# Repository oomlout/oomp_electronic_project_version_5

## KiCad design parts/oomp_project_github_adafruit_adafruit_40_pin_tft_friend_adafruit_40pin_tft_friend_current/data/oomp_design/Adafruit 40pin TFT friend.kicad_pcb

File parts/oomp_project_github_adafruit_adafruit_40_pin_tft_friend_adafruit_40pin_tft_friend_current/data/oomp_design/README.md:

# OOMP KiCad design copy

Open `Adafruit 40pin TFT friend.kicad_pro` (or the `.kicad_pcb` / `.kicad_sch`) in KiCad. Local OOMP libraries are under `libraries/`. Original inputs are preserved in [../original/](../original/).

Only verified unchanged installed KiCad defaults were renamed. Modified, custom, unmatched and unavailable items remain unchanged. Soldering variants are never swapped during conversion. Existing pad coordinates, nets and UUIDs are preserved.

See [conversion_report.yaml](conversion_report.yaml) for every conversion and skip. Copy this directory before editing; regeneration refuses to overwrite edited design files.

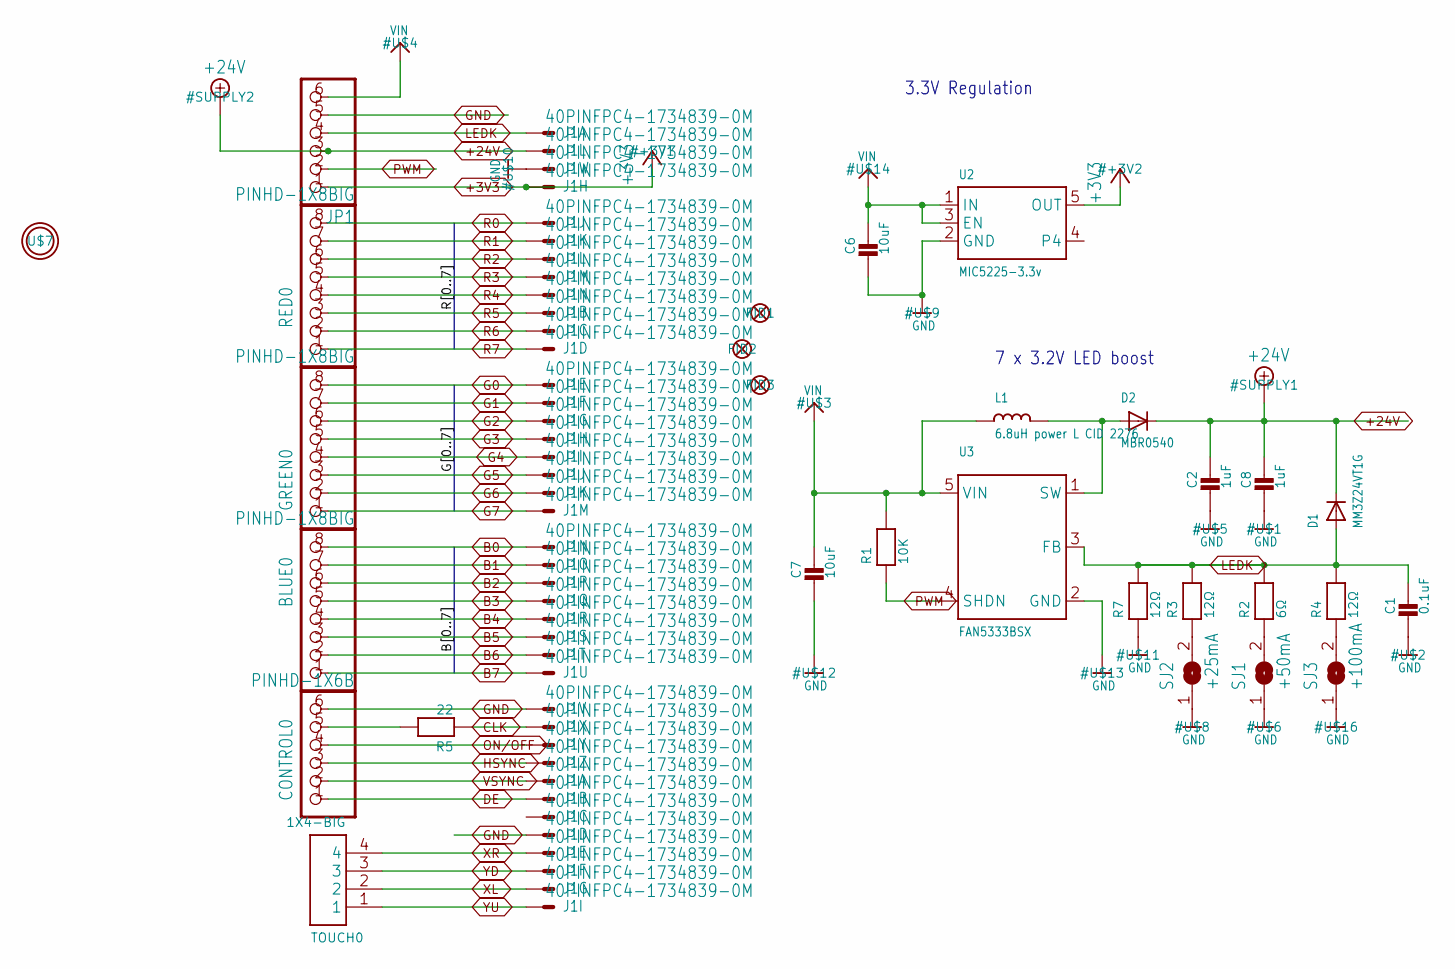
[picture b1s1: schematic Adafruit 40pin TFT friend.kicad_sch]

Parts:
BLUE0: PINHD-1X8BIG; 1X08-BIG
C1: 0.1uF; _0805MP
C2, C8: 1uF; _0805MP
C6, C7: 10uF; _0805MP
CONTROL0: PINHD-1X6B; 1X06-BIG
D1: MM3Z24VT1G; SMADIODE
D2: MBR0540; SOD-123
FID1, FID2, FID3: FIDUCIAL""; FIDUCIAL_1MM
GREEN0: PINHD-1X8BIG; 1X08-BIG
J1: 40PINFPC4-1734839-0M; 4-1734839-0
JP1: PINHD-1X6B; 1X06-BIG
L1: 6.8uH power L CID 2276; INDUCTOR_5X5MM_NR5040_NOTHERMALS
R1: 10K; _0805MP
R2: 6Ω; _0805MP
R3, R4, R7: 12Ω; _0805MP
R5: 22; _0805MP
RED0: PINHD-1X8BIG; 1X08-BIG
SJ1: +50mA; SOLDERJUMPER_ARROW_NOPASTE
SJ2: +25mA; SOLDERJUMPER_ARROW_NOPASTE
SJ3: +100mA; SOLDERJUMPER_ARROW_NOPASTE
TOUCH0: 1X4-BIG; 1X04-BIG
U2: MIC5225-3.3v; SOT23-5
U3: FAN5333BSX; SOT23-5@1
U$7: MOUNTINGHOLE2.5; MOUNTINGHOLE_2.5_PLATED

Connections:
+3V3: J1.4 (MS), JP1.1, U2.5 (OUT)
+24V: C2.1, C8.1, D1.C, D2.C, J1.2 (MS), JP1.3
B0: BLUE0.8, J1.21 (MS)
B1: BLUE0.7, J1.22 (MS)
B2: BLUE0.6, J1.23 (MS)
B3: BLUE0.5, J1.24 (MS)
B4: BLUE0.4, J1.25 (MS)
B5: BLUE0.3, J1.26 (MS)
B6: BLUE0.2, J1.27 (MS)
B7: BLUE0.1, J1.28 (MS)
CLK: J1.30 (MS), R5.1
DE: CONTROL0.1, J1.34 (MS)
G0: GREEN0.8, J1.13 (MS)
G1: GREEN0.7, J1.14 (MS)
G2: GREEN0.6, J1.15 (MS)
G3: GREEN0.5, J1.16 (MS)
G4: GREEN0.4, J1.17 (MS)
G5: GREEN0.3, J1.18 (MS)
G6: GREEN0.2, J1.19 (MS)
G7: GREEN0.1, J1.20 (MS)
GND: C1.2, C2.2, C6.2, C7.2, C8.2, CONTROL0.6, J1.3 (MS), J1.29 (MS), J1.36 (MS), JP1.5, R7.1, SJ1.1, SJ2.1, SJ3.1, U2.2 (GND), U3.2 (GND)
HSYNC: CONTROL0.3, J1.32 (MS)
LEDK: C1.1, D1.A, J1.1 (MSV), JP1.4, R2.2, R3.2, R4.2, R7.2, U3.3 (FB)
unnamed: R2.1, SJ1.2
unnamed: R3.1, SJ2.2
unnamed: R4.1, SJ3.2
unnamed: CONTROL0.5, R5.2
unnamed: D2.A, L1.P$2 (2), U3.1 (SW)
ON/OFF: CONTROL0.4, J1.31 (MS)
PWM: JP1.2, R1.1, U3.4 (SHDN)
R0: J1.5 (MS), RED0.8
R1: J1.6 (MS), RED0.7
R2: J1.7 (MS), RED0.6
R3: J1.8 (MS), RED0.5
R4: J1.9 (MS), RED0.4
R5: J1.10 (MS), RED0.3
R6: J1.11 (MS), RED0.2
R7: J1.12 (MS), RED0.1
VIN: C6.1, C7.1, JP1.6, L1.P$1 (1), R1.2, U2.1 (IN), U2.3 (EN), U3.5 (VIN)
VSYNC: CONTROL0.2, J1.33 (MS)
XL: J1.39 (MS), TOUCH0.2
XR: J1.37 (MS), TOUCH0.4
YD: J1.38 (MS), TOUCH0.3
YU: J1.40 (MS), TOUCH0.1

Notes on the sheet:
3.3V Regulation
7 x 3.2V LED boost

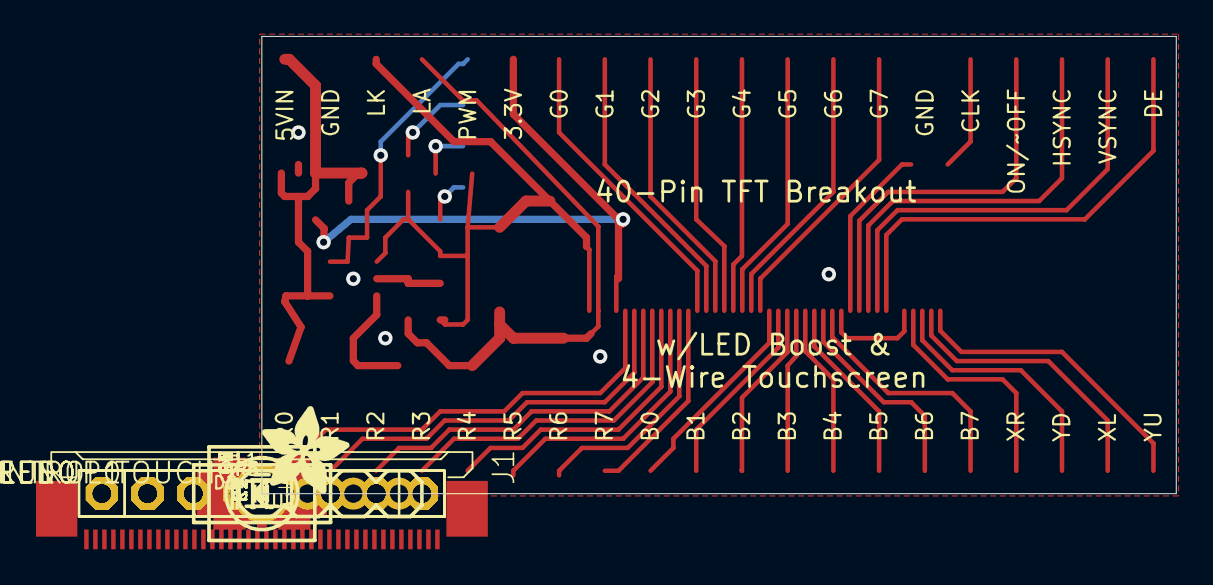
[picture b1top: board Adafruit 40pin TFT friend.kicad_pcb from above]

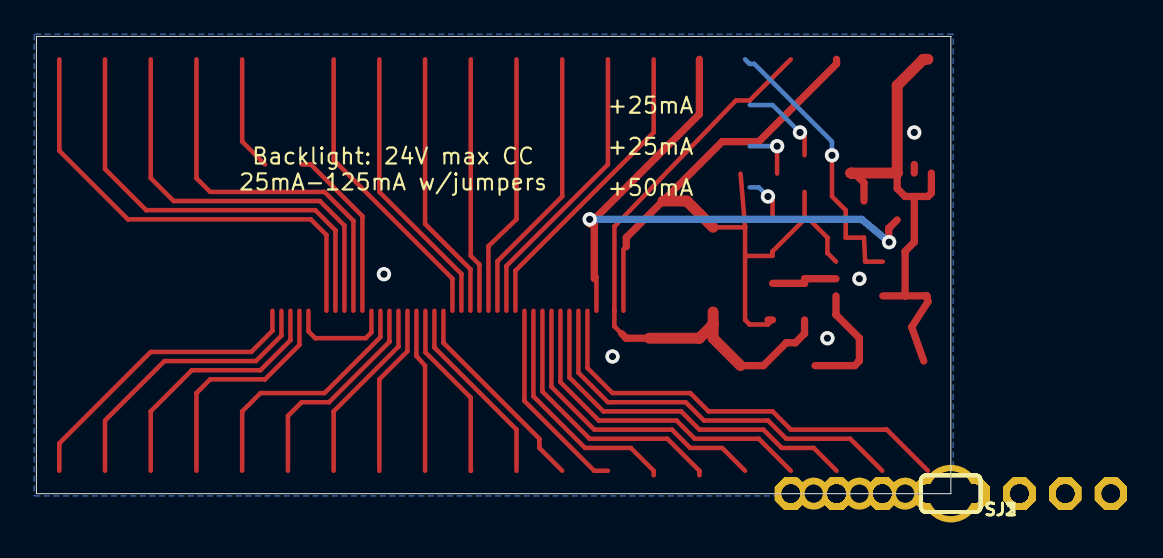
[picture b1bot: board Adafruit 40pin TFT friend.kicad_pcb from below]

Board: 2 copper layers, 50.8 x 25.4 mm, 31 parts (3 on the bottom side), 44 nets.

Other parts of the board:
U$15: ADAFRUIT_5MM

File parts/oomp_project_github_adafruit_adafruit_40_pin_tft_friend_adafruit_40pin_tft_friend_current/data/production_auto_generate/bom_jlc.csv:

Comment,Designator,Footprint,LCSC Part #
,TOUCH0,Adafruit 40pin TFT friend-import-fps:1X04-BIG,C42431795
,"CONTROL0,JP1",Adafruit 40pin TFT friend-import-fps:1X06-BIG,C37208
,RED0,Adafruit 40pin TFT friend-import-fps:1X08-BIG,
,"BLUE0,GREEN0",Adafruit 40pin TFT friend-import-fps:1X08-BIG,C492421
,U$15,Adafruit 40pin TFT friend-import-fps:ADAFRUIT_5MM,
0.1uF,C1,Adafruit 40pin TFT friend-import-fps:_0805MP,
10K,R1,Adafruit 40pin TFT friend-import-fps:_0805MP,C17414
10uF,"C6,C7",Adafruit 40pin TFT friend-import-fps:_0805MP,
12Ω,"R3,R4,R7",Adafruit 40pin TFT friend-import-fps:_0805MP,C2907226
1uF,"C2,C8",Adafruit 40pin TFT friend-import-fps:_0805MP,
22,R5,Adafruit 40pin TFT friend-import-fps:_0805MP,C2907310
40PINFPCM4-1734839-0,J1,Adafruit 40pin TFT friend-import-fps:4-1734839-0,
6.8uH power L CID 2276,L1,Adafruit 40pin TFT friend-import-fps:INDUCTOR_5X5MM_NR5040_NOTHERMALS,
6Ω,R2,Adafruit 40pin TFT friend-import-fps:_0805MP,
FAN5333BSX,U3,Adafruit 40pin TFT friend-import-fps:SOT23-5@1,
MBR0540,D2,Adafruit 40pin TFT friend-import-fps:SOD-123,
MIC5225-3.3v,U2,Adafruit 40pin TFT friend-import-fps:SOT23-5,
MM3Z24VT1G,D1,Adafruit 40pin TFT friend-import-fps:SMADIODE,

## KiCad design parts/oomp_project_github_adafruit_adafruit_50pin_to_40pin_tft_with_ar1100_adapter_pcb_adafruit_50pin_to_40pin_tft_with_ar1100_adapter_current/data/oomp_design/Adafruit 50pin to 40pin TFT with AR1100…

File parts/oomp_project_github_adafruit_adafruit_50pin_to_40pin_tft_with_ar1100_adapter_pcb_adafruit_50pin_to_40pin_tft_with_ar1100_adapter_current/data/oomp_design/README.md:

# OOMP KiCad design copy

Open `Adafruit 50pin to 40pin TFT with AR1100 Adapter.kicad_pro` (or the `.kicad_pcb` / `.kicad_sch`) in KiCad. Local OOMP libraries are under `libraries/`. Original inputs are preserved in [../original/](../original/).

Only verified unchanged installed KiCad defaults were renamed. Modified, custom, unmatched and unavailable items remain unchanged. Soldering variants are never swapped during conversion. Existing pad coordinates, nets and UUIDs are preserved.

See [conversion_report.yaml](conversion_report.yaml) for every conversion and skip. Copy this directory before editing; regeneration refuses to overwrite edited design files.

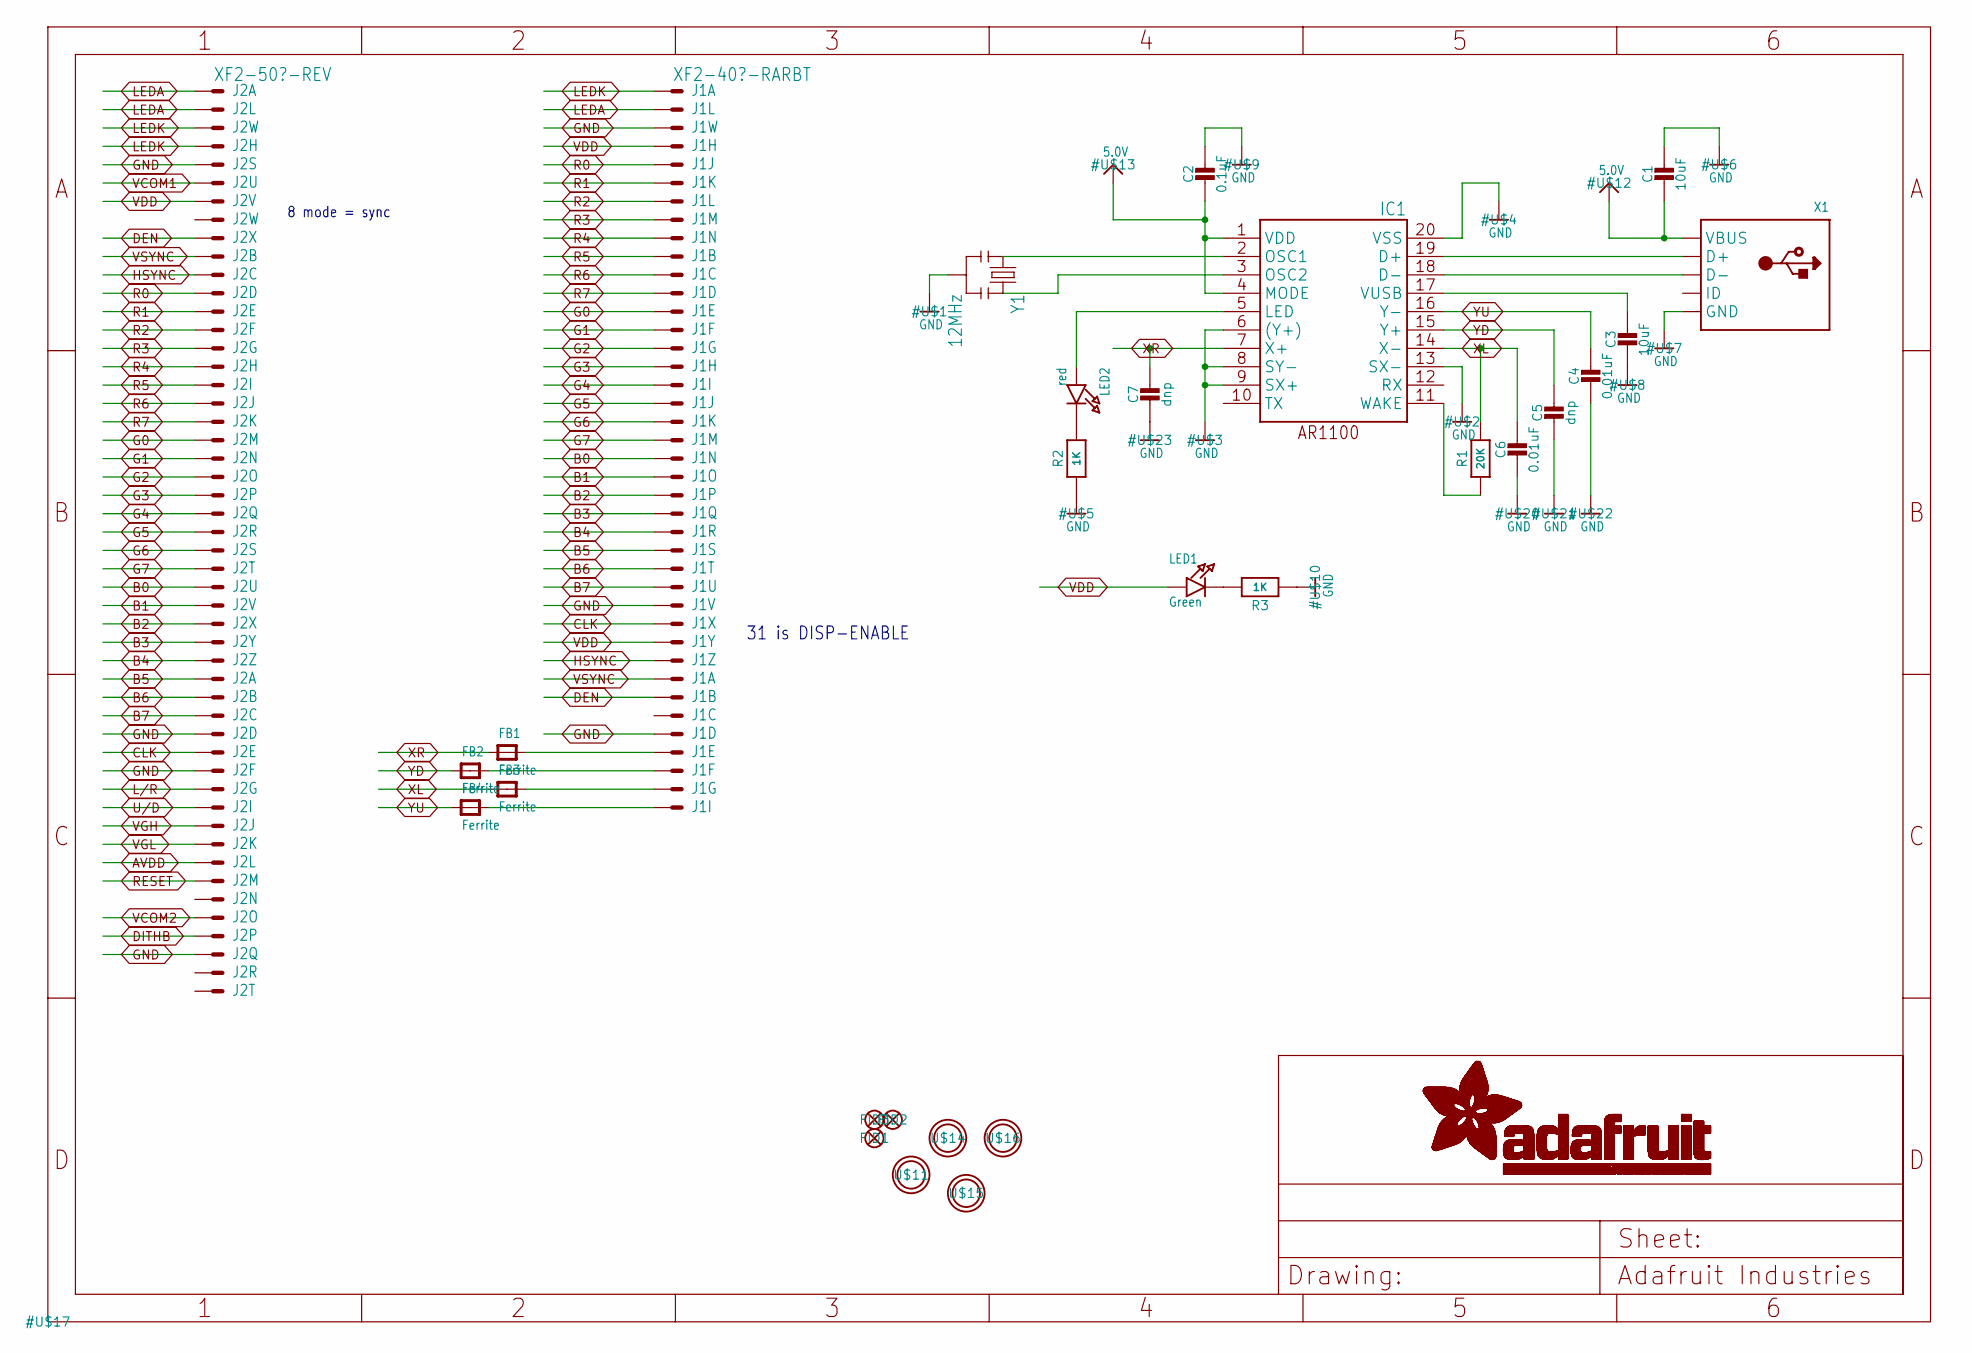
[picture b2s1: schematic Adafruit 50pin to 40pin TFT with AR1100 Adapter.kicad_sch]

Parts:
C1, C3: 10uF; _0805MP
C2: 0.1uF; _0805MP
C4, C6: 0.01uF; _0805MP
C5, C7: dnp; _0805MP
FB1, FB2, FB3, FB4: Ferrite; _0805
FID1, FID2, FID3: FIDUCIAL""; FIDUCIAL_1MM
IC1: AR1100_SSOP; TSSOP20-5.3MMBODY
J1: XF2-40?-RARBT; 4-1734839-0
J2: XF2-50?-REV; 5-1734839-0-REV
LED1: Green; CHIPLED_0805_NOOUTLINE
LED2: red; CHIPLED_0805_NOOUTLINE
R1: 20K; _0805MP
R2, R3: 1K; _0805MP
U$11, U$14, U$15, U$16: MOUNTINGHOLE2.5; MOUNTINGHOLE_2.5_PLATED
X1: USBMINIBLARGE; USB-MINIB_LARGER
Y1: 12MHz; RESONATOR-SMD

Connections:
5.0V: C1.2, C2.2, IC1.1 (VDD), IC1.4 (MODE), X1.VBUS
AVDD: J2.43 (MS)
B0: J1.21 (MS), J2.28 (MS)
B1: J1.22 (MS), J2.29 (MS)
B2: J1.23 (MS), J2.30 (MS)
B3: J1.24 (MS), J2.31 (MS)
B4: J1.25 (MS), J2.32 (MS)
B5: J1.26 (MS), J2.33 (MS)
B6: J1.27 (MS), J2.34 (MS)
B7: J1.28 (MS), J2.35 (MS)
CLK: J1.30 (MS), J2.37 (MS)
D+: IC1.19 (D+), X1.D+
D-: IC1.18 (D-), X1.D-
DEN: J1.34 (MS), J2.9 (MS)
DITHB: J2.47 (MS)
G0: J1.13 (MS), J2.20 (MS)
G1: J1.14 (MS), J2.21 (MS)
G2: J1.15 (MS), J2.22 (MS)
G3: J1.16 (MS), J2.23 (MS)
G4: J1.17 (MS), J2.24 (MS)
G5: J1.18 (MS), J2.25 (MS)
G6: J1.19 (MS), J2.26 (MS)
G7: J1.20 (MS), J2.27 (MS)
GND: C1.1, C2.1, C3.2, C4.2, C5.2, C6.2, C7.2, IC1.6 ((Y+)), IC1.8 (SY-), IC1.9 (SX+), IC1.13 (SX-), IC1.20 (VSS), J1.3 (MS), J1.29 (MS), J1.36 (MS), J2.5 (MS), J2.36 (MS), J2.38 (MS), J2.48 (MS), R2.1, R3.1, X1.GND, X1.GND1 (GND), X1.GND2 (GND), X1.GND3 (GND), X1.GND4 (GND), Y1.2
HSYNC: J1.32 (MS), J2.11 (MS)
L/R: J2.39 (MS)
LEDA: J1.2 (MS), J2.1 (MSV), J2.2 (MS)
LEDK: J1.1 (MSV), J2.3 (MS), J2.4 (MS)
unnamed: IC1.2 (OSC1), Y1.1
unnamed: IC1.3 (OSC2), Y1.3
unnamed: FB1.2, J1.37 (MS)
unnamed: FB2.2, J1.38 (MS)
unnamed: FB3.2, J1.39 (MS)
unnamed: FB4.2, J1.40 (MS)
unnamed: LED2.C, R2.2
unnamed: IC1.5 (LED), LED2.A
unnamed: IC1.11 (WAKE), R1.1
unnamed: LED1.C, R3.2
unnamed: C3.1, IC1.17 (VUSB)
R0: J1.5 (MS), J2.12 (MS)
R1: J1.6 (MS), J2.13 (MS)
R2: J1.7 (MS), J2.14 (MS)
R3: J1.8 (MS), J2.15 (MS)
R4: J1.9 (MS), J2.16 (MS)
R5: J1.10 (MS), J2.17 (MS)
R6: J1.11 (MS), J2.18 (MS)
R7: J1.12 (MS), J2.19 (MS)
RESET: J2.44 (MS)
U/D: J2.40 (MS)
VCOM1: J2.6 (MS)
VCOM2: J2.46 (MS)
VDD: J1.4 (MS), J1.31 (MS), J2.7 (MS), LED1.A
VGH: J2.41 (MS)
VGL: J2.42 (MS)
VSYNC: J1.33 (MS), J2.10 (MS)
XL: C6.1, FB3.1, IC1.14 (X-), R1.2
XR: C7.1, FB1.1, IC1.7 (X+)
YD: C5.1, FB2.1, IC1.15 (Y+)
YU: C4.1, FB4.1, IC1.16 (Y-)

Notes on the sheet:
31 is DISP-ENABLE
8 mode = sync

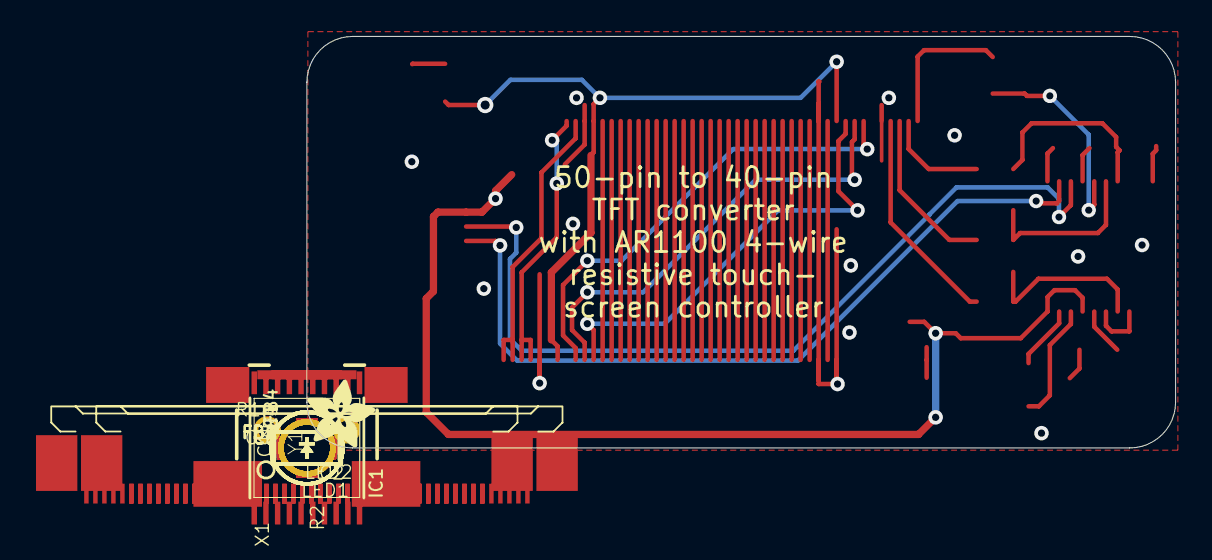
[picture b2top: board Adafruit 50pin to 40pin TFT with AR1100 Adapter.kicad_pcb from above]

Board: 2 copper layers, 48.3 x 22.9 mm, 30 parts (1 on the bottom side), 50 nets.

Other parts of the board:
U$18: ADAFRUIT_TEXT_30MM
U$19: ADAFRUIT_3.5MM

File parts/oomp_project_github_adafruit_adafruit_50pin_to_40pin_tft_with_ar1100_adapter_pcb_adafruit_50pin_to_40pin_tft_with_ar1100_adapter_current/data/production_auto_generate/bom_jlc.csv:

Comment,Designator,Footprint,LCSC Part #
,U$19,ADAFRUIT_3.5MM,
,U$18,ADAFRUIT_TEXT_30MM,
,X1,USB-MINIB_LARGER,
0.01uF,"C4,C6",_0805MP,
0.1uF,C2,_0805MP,
10uF,"C1,C3",_0805MP,
12MHz,Y1,RESONATOR-SMD,
1K,"R2,R3",_0805MP,C17513
20K,R1,_0805MP,
AR1100_SSOP,IC1,TSSOP20-5.3MMBODY,
dnp,"C5,C7",_0805MP,
Ferrite,"FB1,FB2,FB3,FB4",_0805,
Green,LED1,CHIPLED_0805_NOOUTLINE,
red,LED2,CHIPLED_0805_NOOUTLINE,
XF2-40-RARBT,J1,4-1734839-0,
XF2-50-REV,J2,5-1734839-0-REV,

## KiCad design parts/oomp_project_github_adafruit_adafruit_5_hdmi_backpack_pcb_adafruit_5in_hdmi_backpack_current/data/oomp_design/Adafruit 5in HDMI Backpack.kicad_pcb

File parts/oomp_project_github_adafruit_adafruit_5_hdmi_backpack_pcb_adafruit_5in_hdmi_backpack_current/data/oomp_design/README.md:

# OOMP KiCad design copy

Open `Adafruit 5in HDMI Backpack.kicad_pro` (or the `.kicad_pcb` / `.kicad_sch`) in KiCad. Local OOMP libraries are under `libraries/`. Original inputs are preserved in [../original/](../original/).

Only verified unchanged installed KiCad defaults were renamed. Modified, custom, unmatched and unavailable items remain unchanged. Soldering variants are never swapped during conversion. Existing pad coordinates, nets and UUIDs are preserved.

See [conversion_report.yaml](conversion_report.yaml) for every conversion and skip. Copy this directory before editing; regeneration refuses to overwrite edited design files.

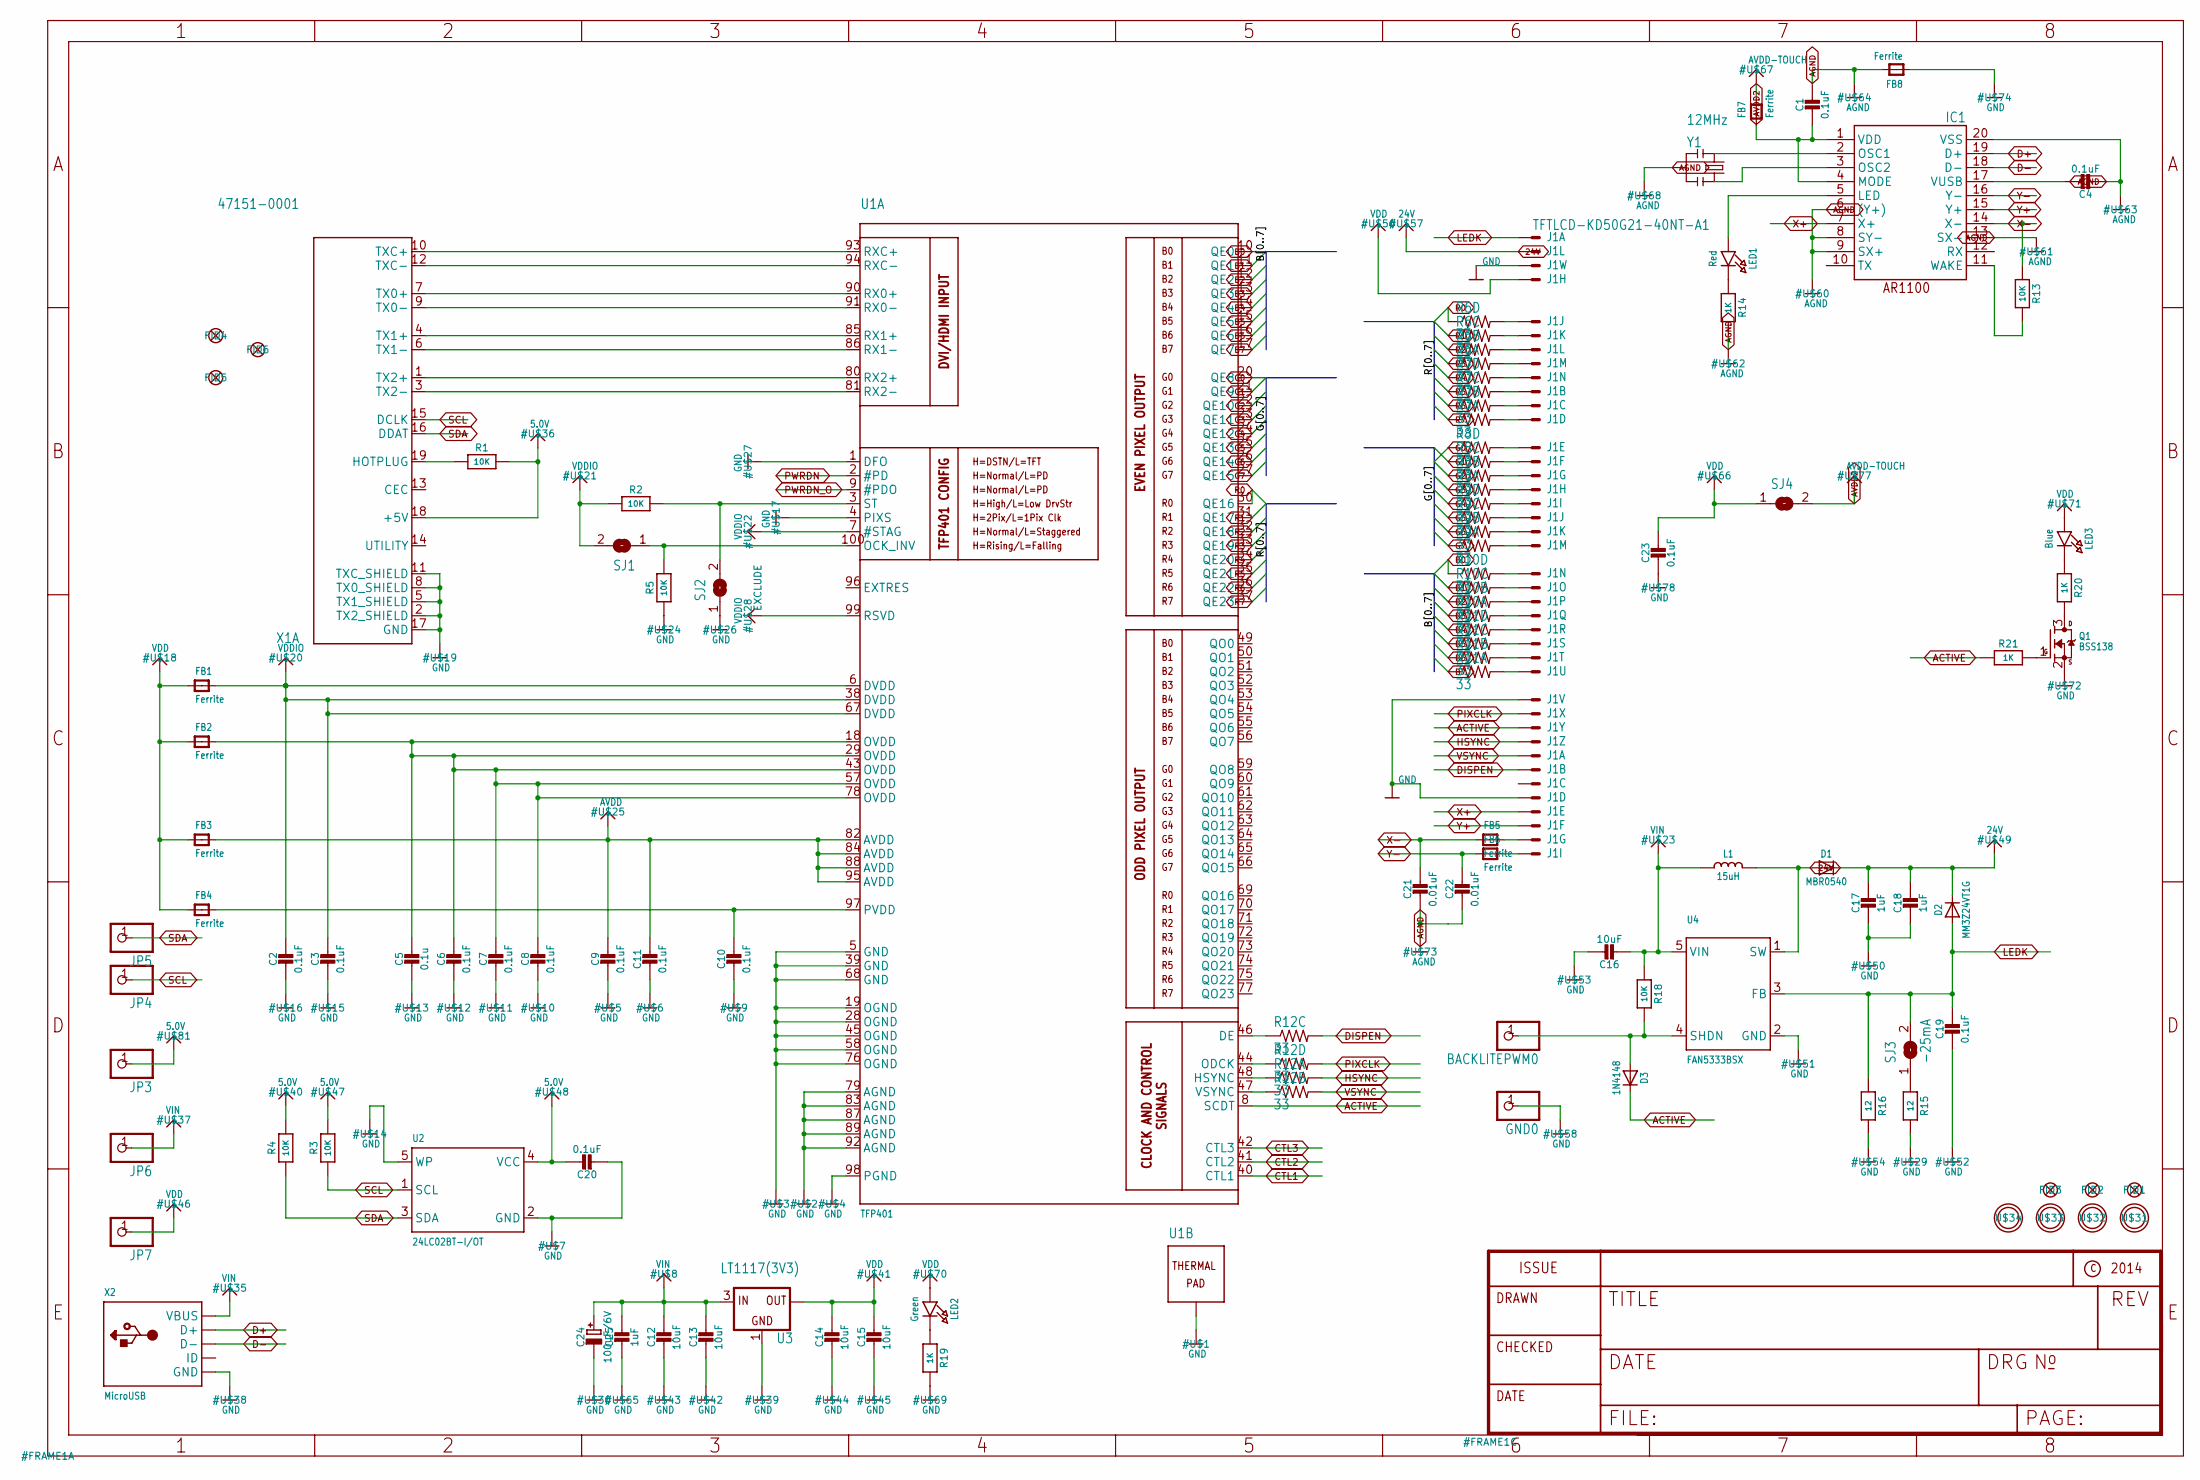
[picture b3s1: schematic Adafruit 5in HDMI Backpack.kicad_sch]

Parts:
BACKLITEPWM0: HEADER-1X1-SMD_MASKHELD_2X2MM; 1X01_SMD_MASKHELD_2X2MM
C1, C2, C3, C7, C8, C9, C10, C11, C19, C20, C23: 0.1uF; 0805-NO
C4, C6: 0.1uF; _0805MP
C5: 0.1u; 0805-NO
C12, C13, C14, C15, C16: 10uF; 0805-NO
C17, C18, C25: 1uF; 0805-NO
C21, C22: 0.01uF; 0805-NO
C24: 100uF/6V; PANASONIC_C
D1: MBR0540; SOD-123
D2: MM3Z24VT1G; SMADIODE
D3: 1N4148; SOD-323
FB1, FB2, FB3, FB4, FB5, FB6, FB7, FB8: Ferrite; _0805MP
FID1, FID2, FID3, FID4, FID5, FID6: FIDUCIAL""; FIDUCIAL_1MM
GND0: HEADER-1X1-SMD_MASKHELD_2X2MM; 1X01_SMD_MASKHELD_2X2MM
IC1: AR1100; TSSOP20-5.3MMBODY
J1: TFTLCD-KD50G21-40NT-A1
JP3, JP4, JP5, JP6, JP7: HEADER-1X1-SMD_MASKHELD_2X2MM; 1X01_SMD_MASKHELD_2X2MM
L1: 15uH; INDUCTOR_5X5MM_NR5040_NOTHERMALS
LED1: Red; CHIPLED_0805_NOOUTLINE
LED2: Green; CHIPLED_0805_NOOUTLINE
LED3: Blue; CHIPLED_0805_NOOUTLINE
Q1: BSS138; SOT23-WIDE
R1, R3, R4, R13, R18: 10K; 0805-NO
R2, R5: 10K; _0805MP
R6, R7, R8, R9, R10, R11, R12: 33; RESPACK_4X0603
R14, R19, R20, R21: 1K; 0805-NO
R15, R16: 12; 0805-NO
SJ1, SJ2: SOLDERJUMPER; SOLDERJUMPER_ARROW_NOPASTE
SJ3: -25mA; SOLDERJUMPER_CLOSEDWIRE
SJ4: SOLDERJUMPERCLOSED; SOLDERJUMPER_CLOSEDWIRE
U1: TFP401; S-PQFP-G100
U2: 24LC02BT-I/OT; SOT23-5
U3: LT1117(3V3); SOT223-R
U4: FAN5333BSX; SOT23-5
U$31, U$32, U$33, U$34: MOUNTINGHOLE3.0; MOUNTINGHOLE_3.0_PLATED
X1: 47151-0001; HDMI_MOLEX_47151-0001_DIMLAYER
X2: MicroUSB; 4UCONN_20329
Y1: 12MHz; RESONATOR-SMD

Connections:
5.0V: C20.1, JP3.1, R1.2, R3.2, R4.2, U2.4 (VCC), X1.18 (+5V)
24V: C17.1, C18.1, D1.C, D2.C, J1.2 (MS)
ACTIVE: D3.C, J1.31 (MS), R21.1, U1.8 (SCDT)
AGND: C1.1, C4.2, C21.2, C22.2, FB8.2, IC1.6 ((Y+)), IC1.8 (SY-), IC1.9 (SX+), IC1.13 (SX-), IC1.20 (VSS), R14.2, Y1.2
ASD: R12.3 (1), U1.46 (DE)
AVDD: C9.1, C11.1, FB3.2, U1.82 (AVDD), U1.84 (AVDD), U1.88 (AVDD), U1.95 (AVDD)
AVDD2: FB7.2, SJ4.2
B0: R10.4 (1), U1.10 (QE0)
B1: R10.3 (1), U1.11 (QE1)
B2: R10.2 (1), U1.12 (QE2)
B3: R10.1, U1.13 (QE3)
B4: R11.4 (1), U1.14 (QE4)
B5: R11.3 (1), U1.15 (QE5)
B6: R11.2 (1), U1.16 (QE6)
B7: R11.1, U1.17 (QE7)
CTL1: U1.40 (CTL1)
CTL2: U1.41 (CTL2)
CTL3: U1.42 (CTL3)
CVB: R12.2 (1), U1.47 (VSYNC)
D+: IC1.19 (D+), X2.D+
D-: IC1.18 (D-), X2.D-
DISPEN: J1.34 (MS), R12.6 (2)
G0: R8.4 (1), U1.20 (QE8)
G1: R8.3 (1), U1.21 (QE9)
G2: R8.2 (1), U1.22 (QE10)
G3: R8.1, U1.23 (QE11)
G4: R9.4 (1), U1.24 (QE12)
G5: R9.3 (1), U1.25 (QE13)
G6: R9.2 (1), U1.26 (QE14)
G7: R9.1, U1.27 (QE15)
GND: C2.2, C3.2, C5.2, C6.2, C7.2, C8.2, C9.2, C10.2, C11.2, C12.2, C13.2, C14.2, C15.2, C16.1, C17.2, C18.2, C19.2, C20.2, C23.2, C24.-, C25.2, FB8.1, GND0.1, J1.3 (MS), J1.29 (MS), J1.36 (MS), Q1.2 (S), R5.1, R15.2, R16.2, R19.2, SJ2.1, U1.1 (DFO), U1.4 (PIXS), U1.5 (GND), U1.19 (OGND), U1.28 (OGND), U1.39 (GND), U1.45 (OGND), U1.58 (OGND), U1.68 (GND), U1.76 (OGND), U1.79 (AGND), U1.83 (AGND), U1.87 (AGND), U1.89 (AGND), U1.92 (AGND), U1.98 (PGND), U1.P$1 (TP), U1.P$2 (TP), U1.P$3 (TP), U1.P$4 (TP), U1.P$5 (TP), U1.P$6 (TP), U1.P$7 (TP), U1.P$8 (TP), U1.P$9 (TP), U1.P$10 (TP), U1.P$11 (TP), U1.P$12 (TP), U1.P$13 (TP), U1.P$14 (TP), U1.P$15 (TP), U1.P$16 (TP), U1.THERMAL (TP), U2.2 (GND), U2.5 (WP), U3.1 (GND), U4.2 (GND), X1.2 (TX2_SHIELD), X1.5 (TX1_SHIELD), X1.8 (TX0_SHIELD), X1.11 (TXC_SHIELD), X1.17 (GND), X1.P$1 (GND), X1.P$2 (GND), X1.P$3 (GND), X1.P$4 (GND), X2.BASE@1 (GND), X2.BASE@2 (GND), X2.GND, X2.SPRT@1 (GND), X2.SPRT@2 (GND), X2.SPRT@3 (GND), X2.SPRT@4 (GND)
HSYNC: J1.32 (MS), R12.8 (2)
LEDK: C19.1, D2.A, J1.1 (MSV), R16.1, SJ3.2, U4.3 (FB)
unnamed: U1.93 (RXC+), X1.10 (TXC+)
unnamed: U1.94 (RXC-), X1.12 (TXC-)
unnamed: U1.90 (RX0+), X1.7 (TX0+)
unnamed: U1.91 (RX0-), X1.9 (TX0-)
unnamed: U1.85 (RX1+), X1.4 (TX1+)
unnamed: U1.86 (RX1-), X1.6 (TX1-)
unnamed: U1.80 (RX2+), X1.1 (TX2+)
unnamed: U1.81 (RX2-), X1.3 (TX2-)
unnamed: R1.1, X1.19 (HOTPLUG)
unnamed: IC1.2 (OSC1), Y1.1
unnamed: IC1.3 (OSC2), Y1.3
unnamed: C4.1, IC1.17 (VUSB)
unnamed: LED2.C, R19.1
unnamed: J1.5 (MS), R6.5 (2)
unnamed: J1.6 (MS), R6.6 (2)
unnamed: J1.7 (MS), R6.7 (2)
unnamed: J1.8 (MS), R6.8 (2)
unnamed: J1.9 (MS), R7.5 (2)
unnamed: J1.10 (MS), R7.6 (2)
unnamed: J1.11 (MS), R7.7 (2)
unnamed: J1.12 (MS), R7.8 (2)
unnamed: J1.13 (MS), R8.5 (2)
unnamed: J1.14 (MS), R8.6 (2)
unnamed: J1.15 (MS), R8.7 (2)
unnamed: J1.16 (MS), R8.8 (2)
unnamed: J1.17 (MS), R9.5 (2)
unnamed: J1.18 (MS), R9.6 (2)
unnamed: J1.19 (MS), R9.7 (2)
unnamed: J1.20 (MS), R9.8 (2)
unnamed: J1.21 (MS), R10.5 (2)
unnamed: J1.22 (MS), R10.6 (2)
unnamed: J1.23 (MS), R10.7 (2)
unnamed: J1.24 (MS), R10.8 (2)
unnamed: J1.25 (MS), R11.5 (2)
unnamed: J1.26 (MS), R11.6 (2)
unnamed: J1.27 (MS), R11.7 (2)
unnamed: C10.1, FB4.2, U1.97 (PVDD)
unnamed: J1.28 (MS), R11.8 (2)
unnamed: IC1.11 (WAKE), R13.2
unnamed: LED1.C, R14.1
unnamed: C5.1, C6.1, C7.1, C8.1, FB2.2, U1.18 (OVDD), U1.29 (OVDD), U1.43 (OVDD), U1.57 (OVDD), U1.78 (OVDD)
unnamed: IC1.5 (LED), LED1.A
unnamed: LED3.C, R20.1
unnamed: Q1.3 (D), R20.2
unnamed: D1.A, L1.P$2 (2), U4.1 (SW)
unnamed: Q1.1 (G), R21.2
unnamed: R15.1, SJ3.1
unnamed: BACKLITEPWM0.1, D3.A, R18.2, U4.4 (SHDN)
unnamed: FB5.2, J1.39 (MS)
unnamed: FB6.2, J1.40 (MS)
unnamed: C1.2, FB7.1, IC1.1 (VDD), IC1.4 (MODE)
OCK_INV: R5.2, SJ1.1, U1.100 (OCK_INV)
PIXCLK: J1.30 (MS), R12.5 (2)
PWRDN: U1.2 (#PD)
PWRDN_O: U1.9 (#PDO)
R0: R6.4 (1), U1.30 (QE16)
R1: R6.3 (1), U1.31 (QE17)
R2: R6.2 (1), U1.32 (QE18)
R3: R6.1, U1.33 (QE19)
R4: R7.4 (1), U1.34 (QE20)
R5: R7.3 (1), U1.35 (QE21)
R6: R7.2 (1), U1.36 (QE22)
R7: R7.1, U1.37 (QE23)
SCL: JP4.1, R3.1, U2.1 (SCL), X1.15 (DCLK)
SDA: JP5.1, R4.1, U2.3 (SDA), X1.16 (DDAT)
ST: R2.2, SJ2.2, U1.3 (ST)
VDD: C14.1, C15.1, C23.1, FB1.1, FB2.1, FB3.1, FB4.1, J1.4 (MS), JP7.1, LED2.A, LED3.A, SJ4.1, U3.2 (OUT), U3.4 (OUT)
VDDIO: C2.1, C3.1, FB1.2, R2.1, SJ1.2, U1.6 (DVDD), U1.7 (#STAG), U1.38 (DVDD), U1.67 (DVDD), U1.99 (RSVD)
VIN: C12.1, C13.1, C16.2, C24.+, C25.1, JP6.1, L1.P$1 (1), R18.1, U3.3 (IN), U4.5 (VIN), X2.VBUS
VSYNC: J1.33 (MS), R12.7 (2)
X+: IC1.7 (X+), J1.37 (MS)
X-: C21.1, FB5.1, IC1.14 (X-), R13.1
XCV: R12.1, U1.48 (HSYNC)
Y+: IC1.15 (Y+), J1.38 (MS)
Y-: C22.1, FB6.1, IC1.16 (Y-)
ZXC: R12.4 (1), U1.44 (ODCK)

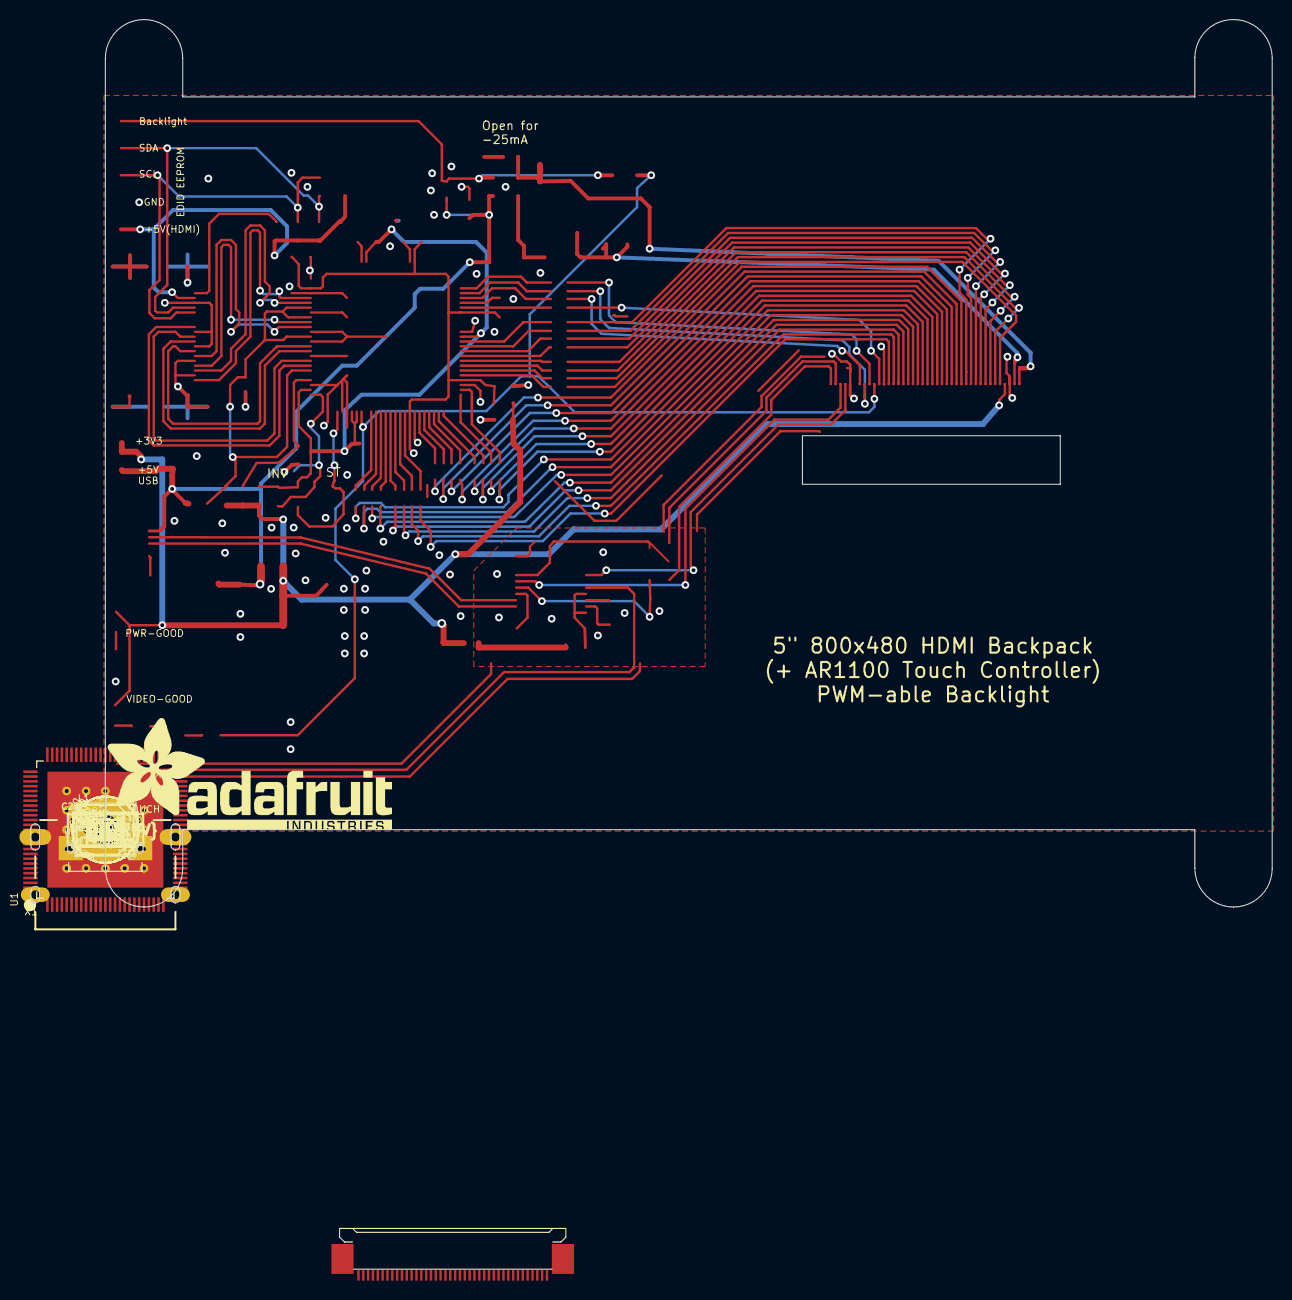
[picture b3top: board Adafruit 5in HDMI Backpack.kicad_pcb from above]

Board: 2 copper layers, 128.4 x 91.8 mm, 93 parts (1 on the bottom side), 104 nets.

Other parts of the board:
U$75: ADAFRUIT_TEXT_30MM
U$76: PCBFEAT-REV-056

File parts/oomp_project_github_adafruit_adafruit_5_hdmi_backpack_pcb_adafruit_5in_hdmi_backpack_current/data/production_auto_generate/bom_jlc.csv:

Comment,Designator,Footprint,LCSC Part #
,"BACKLITEPWM0,GND0,JP3,JP4,JP5,JP6,JP7",Adafruit 5in HDMI Backpack-import-fps:1X01_SMD_MASKHELD_2X2MM,C7501259
,U$75,Adafruit 5in HDMI Backpack-import-fps:ADAFRUIT_TEXT_30MM,
,U$76,Adafruit 5in HDMI Backpack-import-fps:PCBFEAT-REV-056,
0.01uF,"C21,C22",Adafruit 5in HDMI Backpack-import-fps:0805-NO,
0.1u,C5,Adafruit 5in HDMI Backpack-import-fps:0805-NO,
0.1uF,"C1,C2,C3,C7,C8,C9,C10,C11,C19,C20,C23",Adafruit 5in HDMI Backpack-import-fps:0805-NO,
0.1uF,"C4,C6",Adafruit 5in HDMI Backpack-import-fps:_0805MP,
100uF/6V,C24,Adafruit 5in HDMI Backpack-import-fps:PANASONIC_C,
10K,"R1,R3,R4,R13,R18",Adafruit 5in HDMI Backpack-import-fps:0805-NO,C17414
10K,"R2,R5",Adafruit 5in HDMI Backpack-import-fps:_0805MP,C17414
10uF,"C12,C13,C14,C15,C16",Adafruit 5in HDMI Backpack-import-fps:0805-NO,
12,"R15,R16",Adafruit 5in HDMI Backpack-import-fps:0805-NO,C2907226
12MHz,Y1,Adafruit 5in HDMI Backpack-import-fps:RESONATOR-SMD,
15uH,L1,Adafruit 5in HDMI Backpack-import-fps:INDUCTOR_5X5MM_NR5040_NOTHERMALS,
1K,"R14,R19,R20,R21",Adafruit 5in HDMI Backpack-import-fps:0805-NO,C17513
1N4148,D3,Adafruit 5in HDMI Backpack-import-fps:SOD-323,
1uF,"C17,C18,C25",Adafruit 5in HDMI Backpack-import-fps:0805-NO,
24LC02BT-I/OT,U2,Adafruit 5in HDMI Backpack-import-fps:SOT23-5,
33,"R6,R7,R8,R9,R10,R11,R12",Adafruit 5in HDMI Backpack-import-fps:RESPACK_4X0603,C23140
47151-0001,X1,Adafruit 5in HDMI Backpack-import-fps:HDMI_MOLEX_47151-0001_DIMLAYER,
AR1100,IC1,Adafruit 5in HDMI Backpack-import-fps:TSSOP20-5.3MMBODY,
Blue,LED3,Adafruit 5in HDMI Backpack-import-fps:CHIPLED_0805_NOOUTLINE,
BSS138,Q1,Adafruit 5in HDMI Backpack-import-fps:SOT23-WIDE,C52895
FAN5333BSX,U4,Adafruit 5in HDMI Backpack-import-fps:SOT23-5,
Ferrite,"FB1,FB2,FB3,FB4,FB5,FB6,FB7,FB8",Adafruit 5in HDMI Backpack-import-fps:_0805MP,
Green,LED2,Adafruit 5in HDMI Backpack-import-fps:CHIPLED_0805_NOOUTLINE,
LT1117(3V3),U3,Adafruit 5in HDMI Backpack-import-fps:SOT223-R,
MBR0540,D1,Adafruit 5in HDMI Backpack-import-fps:SOD-123,
MicroUSB,X2,Adafruit 5in HDMI Backpack-import-fps:4UCONN_20329,
MM3Z24VT1G,D2,Adafruit 5in HDMI Backpack-import-fps:SMADIODE,
Red,LED1,Adafruit 5in HDMI Backpack-import-fps:CHIPLED_0805_NOOUTLINE,
TFP401,U1,Adafruit 5in HDMI Backpack-import-fps:S-PQFP-G100,
TFTLCD-KD50G21-40NT-A1,J1,Adafruit 5in HDMI Backpack-import-fps:TFTLCD-KD50G21-40NT-A1,
